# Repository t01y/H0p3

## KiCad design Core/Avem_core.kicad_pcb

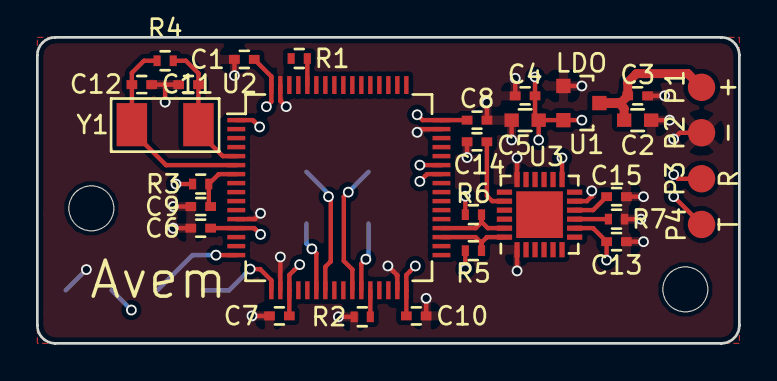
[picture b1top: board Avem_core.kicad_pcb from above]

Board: 4 copper layers, 39.0 x 17.0 mm, 30 parts (0 on the bottom side), 15 nets.

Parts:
C1, C3, C4, C6, C7, C8, C9, C10, C13, C15: 104; C_0402
C2, C5: 106; C_0603
C11, C12: 20pF; C_0402
C14: 2200pF; C_0402
P1: +; Measurement_Point_Round-SMD-Pad_Small
P2: -; Measurement_Point_Round-SMD-Pad_Small
P3: R; Measurement_Point_Round-SMD-Pad_Small
P4: T; Measurement_Point_Round-SMD-Pad_Small
R1, R2, R3: 10K; R_0402
R4: 1M; R_0402
R5, R6, R7: 4.7K; R_0402
U1: LDO; SOT-23
U2: STM32F103RCT6; LQFP-64_10x10mm_Pitch0.5mm
U3: MPU6050; QFN-24-1EP_4x4mm_Pitch0.5mm
Y1: 8MHz; SMD-5032

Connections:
3V3: C1.1, C4.1, C5.1, C6.1, C7.1, C8.1, C10.1, C13.2, R3.1, R5.1, R6.1, U1.2, U2.1, U2.13, U2.19, U2.32, U2.48, U2.64, U3.8, U3.13
+3V3: C2.1, C3.1, P1.1, U1.3
BOOT0: R1.2, U2.60
BOOT1: R2.2, U2.28
GND: C1.2, C2.2, C3.2, C4.2, C5.2, C6.2, C7.2, C8.2, C9.2, C10.2, C11.2, C12.2, C13.1, C14.2, C15.2, P2.1, R2.1, R7.1, U1.1, U2.12, U2.18, U2.31, U2.47, U2.63, U3.1, U3.11, U3.18
IMU_SCL: R6.2, U2.36, U3.23
IMU_SDA: R5.2, U2.35, U3.24
unnamed: C14.1, U3.20
unnamed: C15.1, U3.10
unnamed: R7.2, U3.9
OSCIN: C11.1, R4.2, U2.5, Y1.1
OSCOUT: C12.1, R4.1, U2.6, Y1.2
RESET: C9.1, R3.2, U2.7
USART1_RX: P3.1, U2.43
USART1_TX: P4.1, U2.42

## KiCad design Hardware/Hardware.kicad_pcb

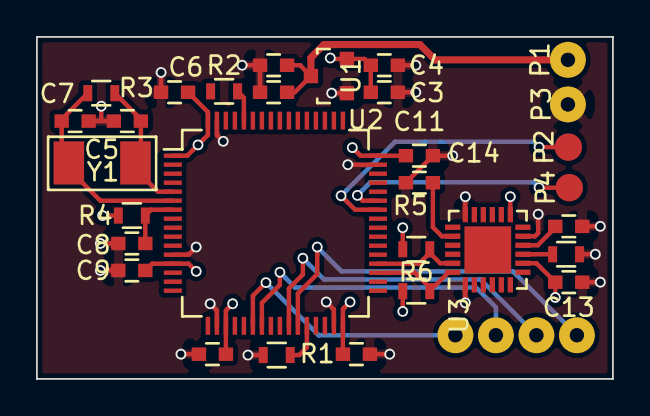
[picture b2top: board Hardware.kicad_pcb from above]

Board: 4 copper layers, 32.0 x 19.0 mm, 34 parts (0 on the bottom side), 19 nets.

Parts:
C1, C4: 106; C_0603
C2, C3, C6, C8, C9, C10, C11, C12, C13, C15: 104; C_0603
C5, C7: 20pF; C_0603
C14: 2200pF; C_0603
P1: +; SolderWirePad_single_0-8mmDrill
P2: TX; Measurement_Point_Round-SMD-Pad_Small
P3: -; SolderWirePad_single_0-8mmDrill
P4: RX; Measurement_Point_Round-SMD-Pad_Small
P5: 1; SolderWirePad_single_0-8mmDrill
P6: 2; SolderWirePad_single_0-8mmDrill
P7: 3; SolderWirePad_single_0-8mmDrill
P8: 4; SolderWirePad_single_0-8mmDrill
R1, R2, R4: 10K; R_0603
R3: 1M; R_0603
R5, R6, R7: 4.7K; R_0603
U1: LDO; SOT-23
U2: STM32F103RCT6; LQFP-64_10x10mm_Pitch0.5mm
U3: MPU6050; QFN-24-1EP_4x4mm_Pitch0.5mm
Y1: 8MHz; SMD-5032

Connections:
3V3: C3.1, C4.1, C6.1, C9.1, C10.1, C11.1, C12.1, C13.2, R4.1, R5.2, R6.1, U1.2, U2.1, U2.13, U2.19, U2.32, U2.48, U2.64, U3.8, U3.13
+3V3: C1.1, C2.1, P1.1, U1.3
BLDC1: P5.1, U2.22
BLDC2: P6.1, U2.23
BLDC3: P7.1, U2.26
BLDC4: P8.1, U2.27
BOOT0: R2.2, U2.60
BOOT1: R1.2, U2.28
GND: C1.2, C2.2, C3.2, C4.2, C5.2, C6.2, C7.2, C8.2, C9.2, C10.2, C11.2, C12.2, C13.1, C14.2, C15.2, P3.1, R1.1, R7.2, U1.1, U2.12, U2.18, U2.31, U2.47, U2.63, U3.1, U3.11, U3.18
IMU_SCL: R6.2, U2.36, U3.23
IMU_SDA: R5.1, U2.35, U3.24
unnamed: C14.1, U3.20
unnamed: C15.1, U3.10
unnamed: R7.1, U3.9
OSCIN: C5.1, R3.1, U2.5, Y1.1
OSCOUT: C7.1, R3.2, U2.6, Y1.2
RESET: C8.1, R4.2, U2.7
USART_RX: P4.1, U2.43
USART_TX: P2.1, U2.42

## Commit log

2016-10-17 First Init
2016-10-17 Mark
2016-10-17 Basic Done
2016-10-17 Update Footprint
2016-10-18 PCB Layout Done And Add Gerber Files
2016-10-26 Init Development
2016-11-11 RTOS Learning
2016-11-12 [MOD]: Fixed
2016-11-12 [MOD] Update
2016-11-12 [MOD] Changed Titles
2016-11-12 [MOD] Fixed
2016-11-12 [MOD]: Delete Space
2016-11-12 [MOD]: Add Tab
2016-11-13 Add Comment
2016-11-13 [MOD]: Enhancement
2016-11-13 [MOD]: Add Comments of Enhancement
2016-11-21 [ADD]: FreeRTOS, [MOD]:
2016-11-21 [MOD]: Modified framework of Makefile *IMPORTANT*
2016-11-22 [ADD]: Add RTOS Sources
2016-11-22 [MOD] FreeRTOS Running Success
2016-11-22 [DEL]: portasm.s
2016-11-22 [MOD]: Needn't Define configUSE_TIMERS to 0, because this is default
2016-12-10 [MOD]: Deleted File 'do_flash.pl'
2016-12-11 [MOD]: Removed Backup File
2016-12-18 feature:(uart) Component
2016-12-18 refactor:(objdump) Enhancement
2016-12-18 fix:(objdump) Update
2017-04-20 feat: (4 Layer)
2017-04-22 doc: 4 layer PCB
2017-04-30 Clean files of FreeRTOS
2017-04-30 feat: (uart) init
2017-04-30 Refactor
2017-04-30 feat: (imu Comput)
2017-05-02 feat: (test)
2017-05-02 feat: (OLED)
2017-05-02 feat: (view port)
2017-05-03 refactor: (delay) Removed delay functions, Now the FPS is 12.8
2017-05-03 feat: (RGB) 8 bits RGB to 5:6:5 RGB Transfer function
2017-05-03 fix: (oled_send2Bytes)
2017-05-03 fix: (oled_send2Bytes) Order
2017-05-06 feat: (IMU)
2017-05-11 fix: (IMU) Initialization
2017-05-11 fix: (main) Typo
2017-05-13 feat: (Core)
2017-05-17 doc: (platform)
2017-05-20 refct: (IMU_SOFTFIX) New Plathform
2017-06-05 feat: (Client)
2017-06-05 feat: (IAP) jump to built-in bootloader
2017-06-05 feat: (make isp)
2017-06-12 feat: (dmp)
2017-06-12 feat: (DMP) Update
2017-06-12 fix: (Systick)
2017-06-19 doc: modifed title
2017-07-06 feat: (gcc) echo messages
2017-07-14 doc:(RM)
